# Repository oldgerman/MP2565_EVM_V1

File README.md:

# MP2565 评估板 V1.0 

## PCB尺寸

## B.O.M

|   NAME  |   VALUE   | PACKAGE |
| ------- | --------- | ------- |
| C1      | 10uF/50V  | 1206    |
| C2      | 22uF/16V  | 1206    |
| C3      | 150pF/50V | 0603    |
| C4      | 100nF/50V | 0603    |
| D1      | SS34F     | SMAF    |
| L1      | 15uH      | L0630   |
| R1      | 210k      | 0603    |
| R2      | 40.2k     | 0603    |
| R3      | 100k      | 0603    |
| R4      | 17.4k     | 0603    |
| R5      | 100k      | 0603    |
| R6      | 200k      | 0603    |
| U1      | MP2565DN  | ESOP8   |
| J1 J2   | KP301-2P  | 3.81mm  |

## 参数

典型输出5V/2.5A, 建议输入电压12-24V，开关频率500KHz

## 适用MP1584

此电路板基本按照datasheet的示例布板，修改R4为24.9k可以Pin to Pin使用MP1584，对于MP2565，R4为17.4k，详见datasheet P15和P16

## MP2565 与 MP1584

MP2565相当于MP1584的高压版本，相比MP1584，MosFet耐压从28V提高到50V，对24V电压降压稳压更保险

## 注意

若使用40V以上的输入电源，D1需要换成SS36，或同等规格的Schottky，请自行更改焊盘

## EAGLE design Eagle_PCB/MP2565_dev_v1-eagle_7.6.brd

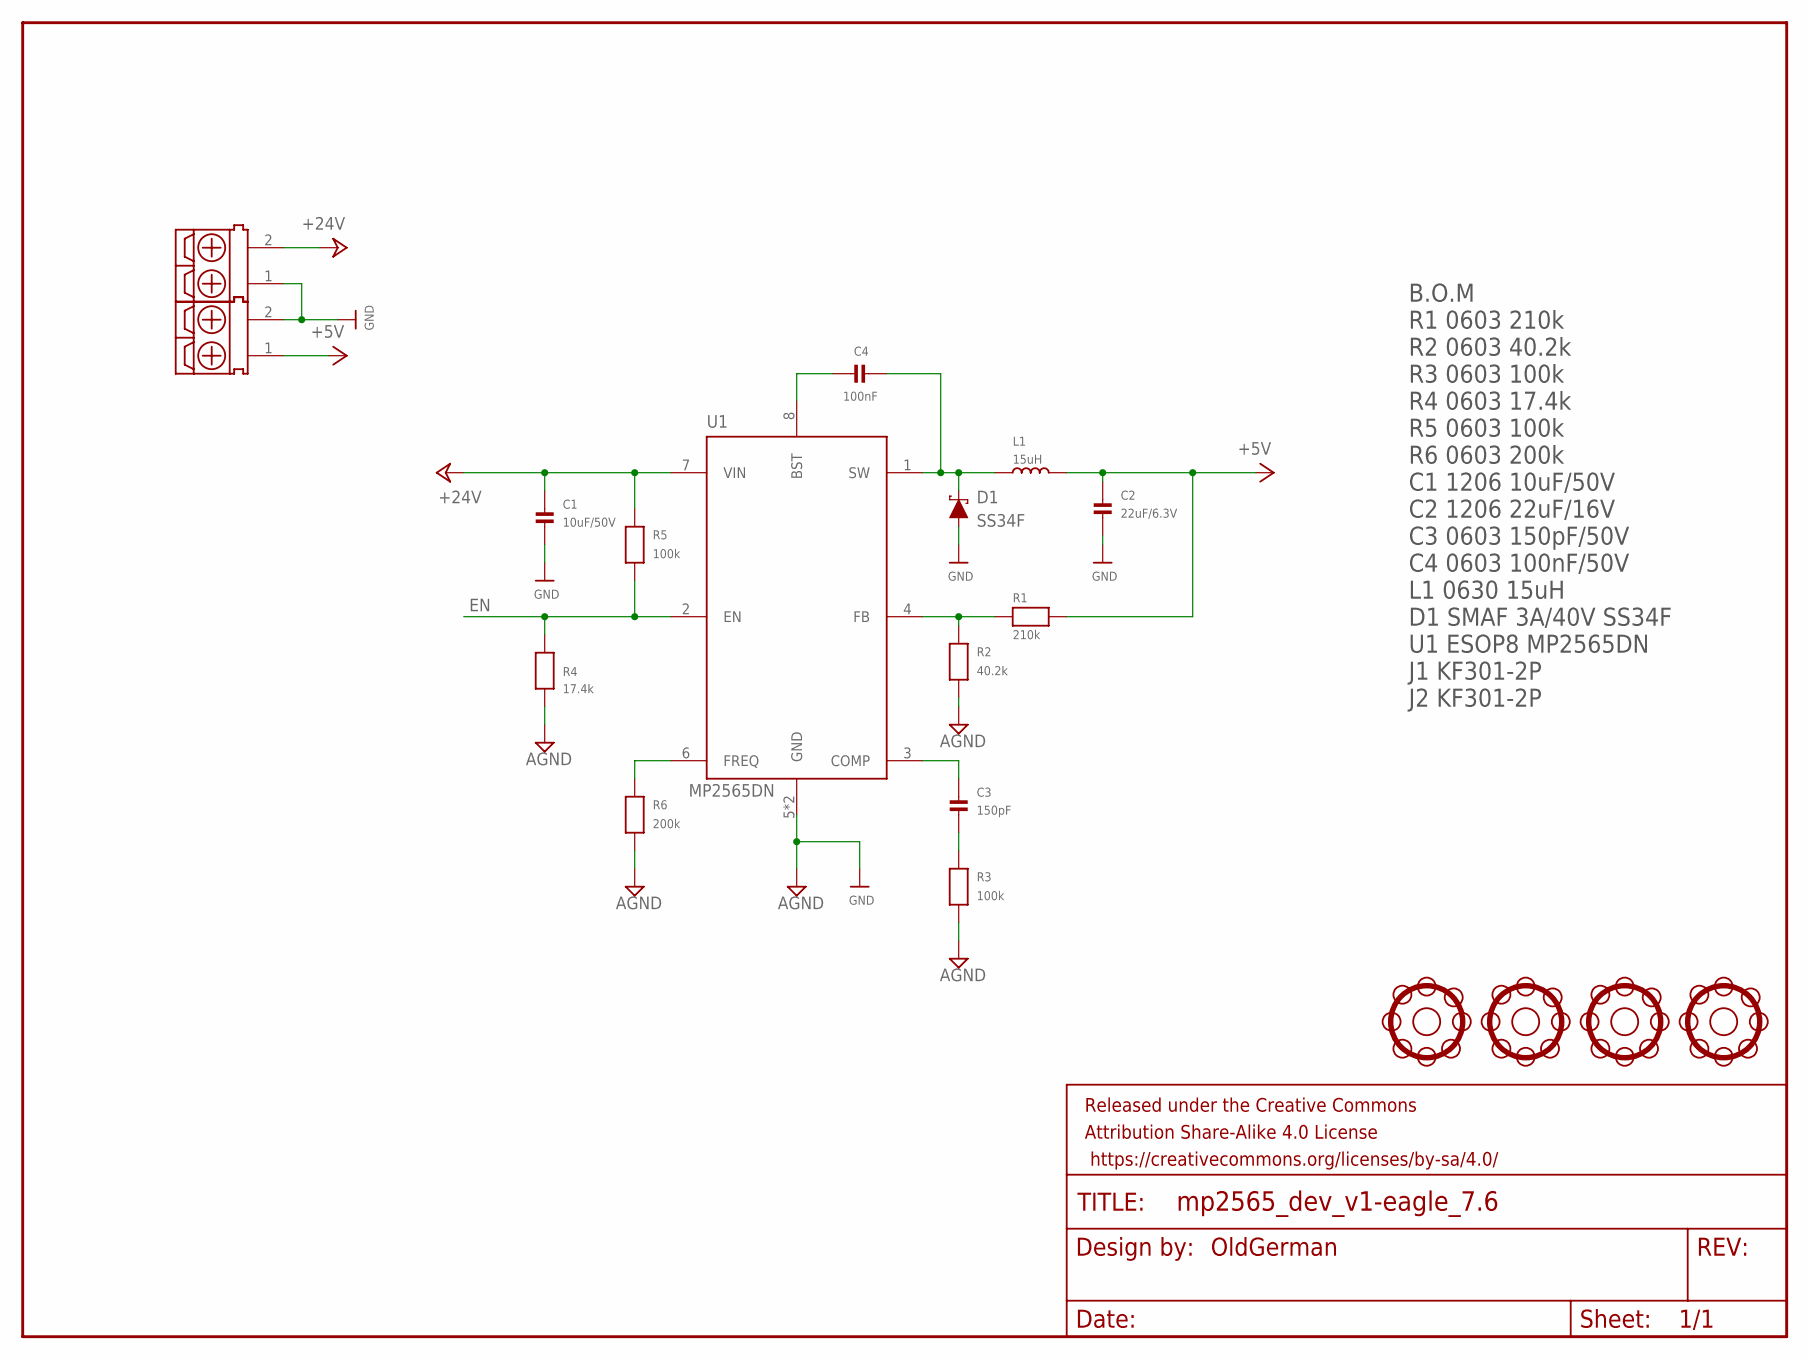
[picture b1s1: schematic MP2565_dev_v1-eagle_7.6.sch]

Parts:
C1: 10uF/50V; 1206
C2: 22uF/6.3V; 1206
C3: 150pF; 0603
C4: 100nF; 0603
D1: SS34F; SMAF
FRAME1: FRAME-LETTER; CREATIVE_COMMONS
J1, J2: KF301_2P-5.0MM; KF301__2P-5.0MM
L1: 15uH; L0630
R1: 210k; 0603
R2: 40.2k; 0603
R3, R5: 100k; 0603
R4: 17.4k; 0603
R6: 200k; 0603
U1: MP2565DN; ESOP8L-1.27-5X3.9MM
U$13, U$14, U$15, U$16: SUN_HOLE_M3

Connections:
+5V: C2.1, J2.1, L1.2, R1.2
+24V: C1.1, J1.2, R5.2, U1.7 (VIN)
EN: R4.1, R5.1, U1.2 (EN)
GND: C1.2, C2.2, D1.A, J1.1, J2.2, R2.1, R3.1, R4.2, R6.1, U1.5 (GND), U1.PAD (GND)
unnamed: C4.2, D1.C, L1.1, U1.1 (SW)
unnamed: C4.1, U1.8 (BST)
unnamed: R1.1, R2.2, U1.4 (FB)
unnamed: C3.2, R3.2
unnamed: R6.2, U1.6 (FREQ)
unnamed: C3.1, U1.3 (COMP)

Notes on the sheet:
B.O.M R1 0603 210k R2 0603 40.2k R3 0603 100k R4 0603 17.4k R5 0603 100k R6 0603 200k C1 1206 10uF/50V C2 1206 22uF/16V C3 0603 150pF/50V C4 0603 100nF/50V L1 0630 15uH D1 SMAF 3A/40V SS34F U1 ESOP8 MP2565DN J1 KF301-2P J2 KF301-2P
OldGerman

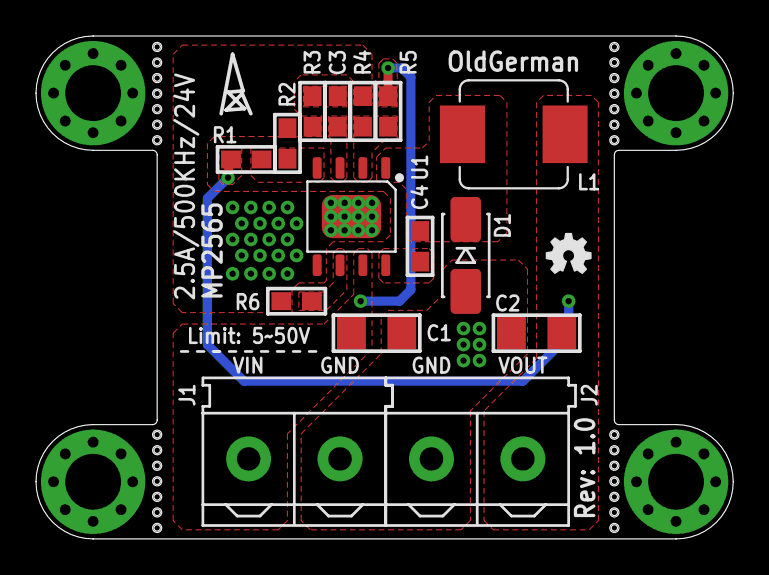
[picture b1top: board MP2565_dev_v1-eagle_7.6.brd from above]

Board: 2 copper layers, 38.7 x 27.9 mm, 21 parts (0 on the bottom side), 10 nets.

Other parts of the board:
U$1: OSHW-LOGO-MINI

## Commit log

2020-06-29 MP2565_EVM_V1
2020-08-05 增加了Eagle7.X版本

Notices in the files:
parts and their libraries:
microbuilder: This work is placed in the public domain, and may be freely used for commercial and non-commercial work with the following conditions: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
SparkFun-Aesthetics: Licensing: Creative Commons ShareAlike 4.0 International - https://creativecommons.org/licenses/by-sa/4.0
